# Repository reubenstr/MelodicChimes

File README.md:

# MelodicChimes

Melodic Chimes is a three string auto-tuning wall chime playing MIDI files created in MuseScore.

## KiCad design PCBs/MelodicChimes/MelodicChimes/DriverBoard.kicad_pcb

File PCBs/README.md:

# PCBs

PCBs created in the free version of DipTrace found here https://diptrace.com/

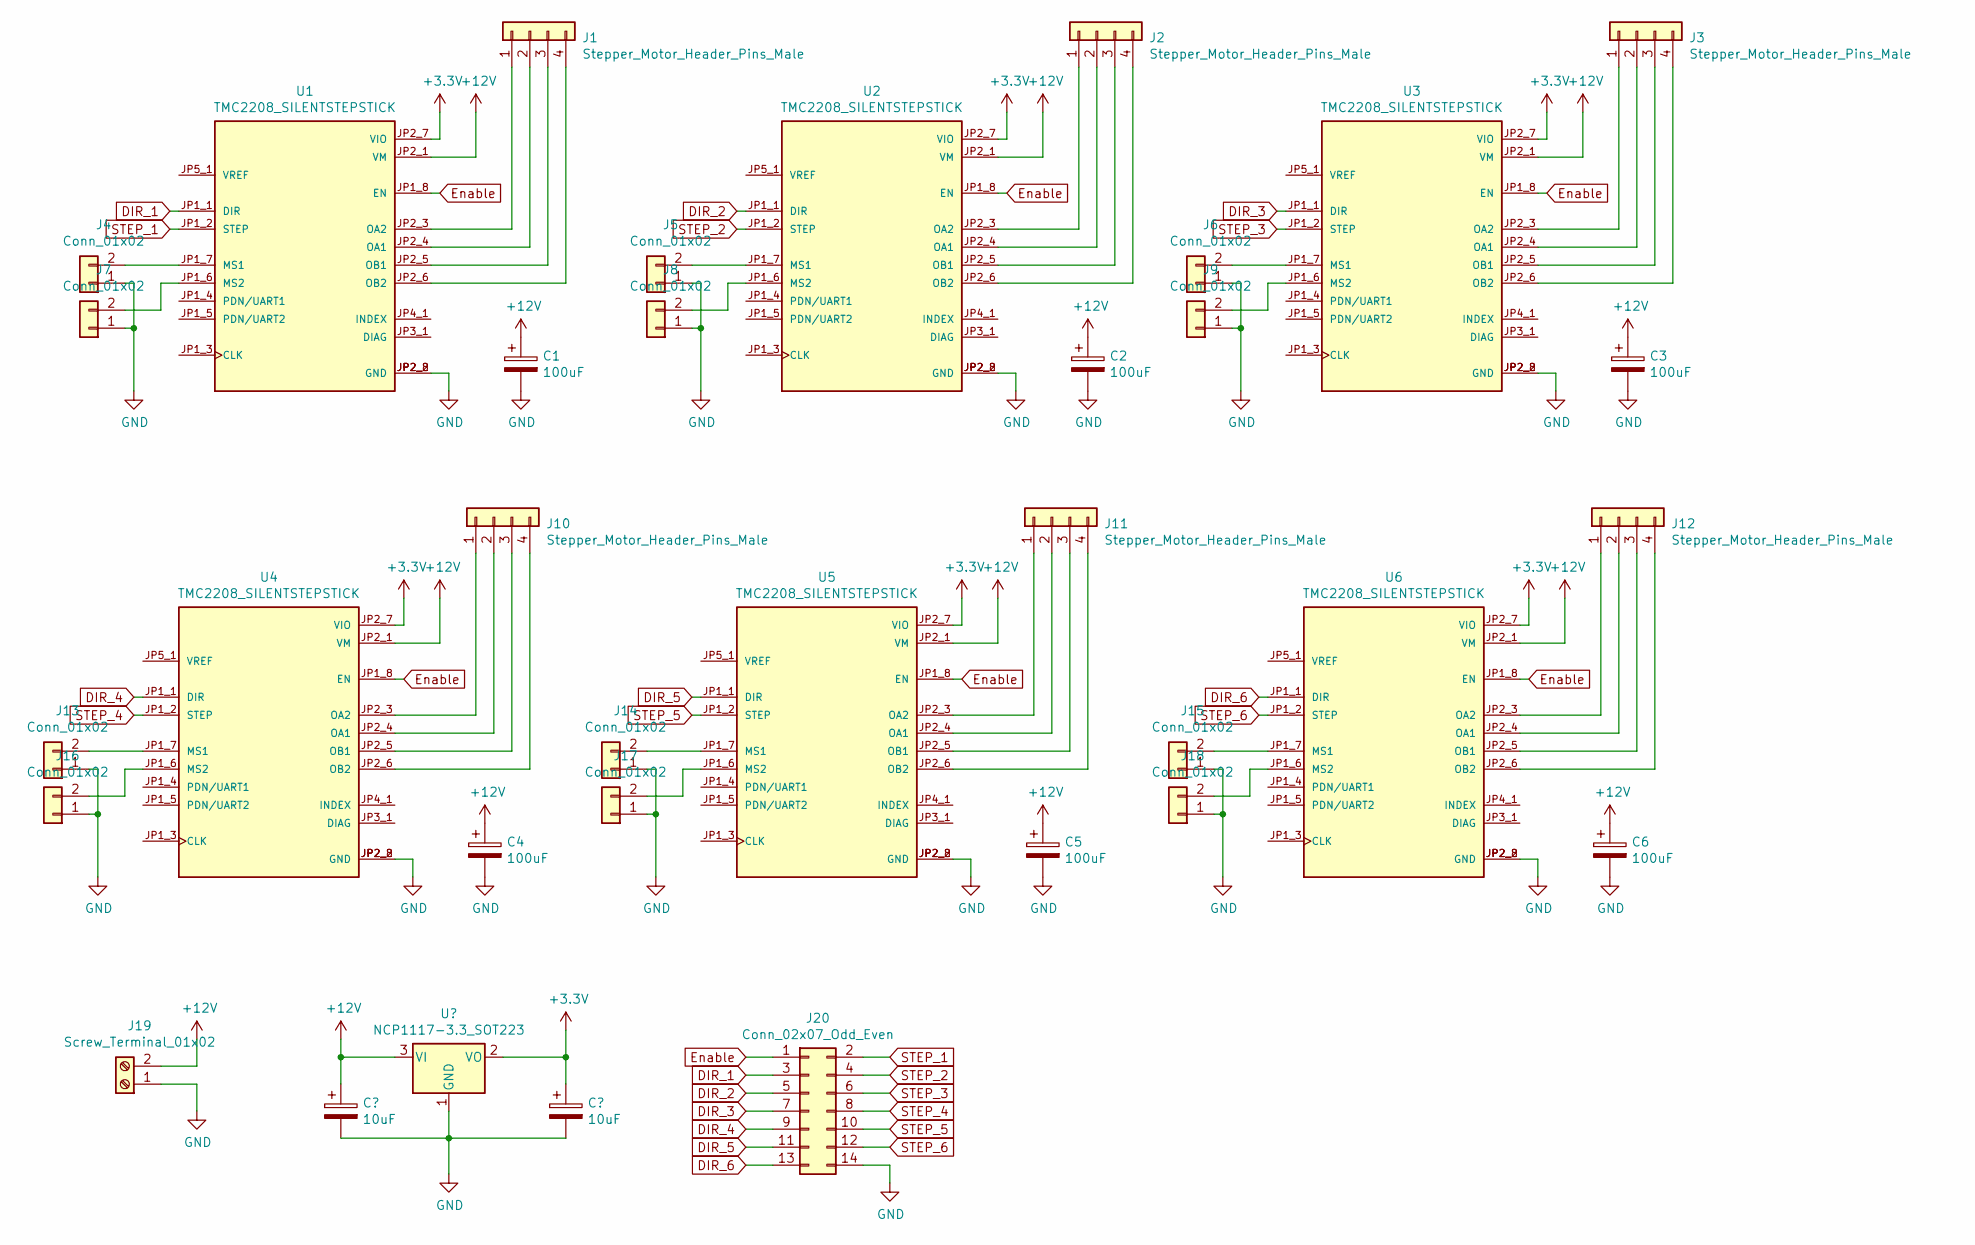
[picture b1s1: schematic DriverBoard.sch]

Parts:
C1, C2, C3, C4, C5, C6: 100uF; CP_Radial_D6.3mm_P2.50mm
J1, J2, J3, J10, J11, J12: Stepper_Motor_Header_Pins_Male; Stepper_Motor_0.100_Pins_Male
J4, J5, J6, J7, J8, J9, J13, J14, J15, J16, J17, J18: Conn_01x02; PinHeader_1x02_P2.54mm_Vertical
J19: Screw_Terminal_01x02; TerminalBlock_TE_282834-2_1x02_P2.54mm_Horizontal
J20: Conn_02x07_Odd_Even; PinHeader_2x07_P2.54mm_Vertical
U1, U2, U3, U4, U5, U6: TMC2208_SILENTSTEPSTICK; MODULE_TMC2208_SILENTSTEPSTICK; PARTREV v11

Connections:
+3V3: U1.JP2_7 (VIO), U2.JP2_7 (VIO), U3.JP2_7 (VIO), U4.JP2_7 (VIO), U5.JP2_7 (VIO), U6.JP2_7 (VIO); also elsewhere on the board
+12V: C1.1, C2.1, C3.1, C4.1, C5.1, C6.1, J19.2, U1.JP2_1 (VM), U2.JP2_1 (VM), U3.JP2_1 (VM), U4.JP2_1 (VM), U5.JP2_1 (VM), U6.JP2_1 (VM); also elsewhere on the board
DIR_1: J20.3, U1.JP1_1 (DIR)
DIR_2: J20.5, U2.JP1_1 (DIR)
DIR_3: J20.7, U3.JP1_1 (DIR)
DIR_4: J20.9, U4.JP1_1 (DIR)
DIR_5: J20.11, U5.JP1_1 (DIR)
DIR_6: J20.13, U6.JP1_1 (DIR)
Enable: J20.1, U1.JP1_8 (EN), U2.JP1_8 (EN), U3.JP1_8 (EN), U4.JP1_8 (EN), U5.JP1_8 (EN), U6.JP1_8 (EN)
GND: C1.2, C2.2, C3.2, C4.2, C5.2, C6.2, J4.1, J5.1, J6.1, J7.1, J8.1, J9.1, J13.1, J14.1, J15.1, J16.1, J17.1, J18.1, J19.1, J20.14, U1.JP2_2 (GND), U1.JP2_8 (GND), U2.JP2_2 (GND), U2.JP2_8 (GND), U3.JP2_2 (GND), U3.JP2_8 (GND), U4.JP2_2 (GND), U4.JP2_8 (GND), U5.JP2_2 (GND), U5.JP2_8 (GND), U6.JP2_2 (GND), U6.JP2_8 (GND); also elsewhere on the board
unnamed: J1.1 (1B), U1.JP2_3 (OA2)
unnamed: J1.2 (1A), U1.JP2_4 (OA1)
unnamed: J1.3 (2A), U1.JP2_5 (OB1)
unnamed: J1.4 (2B), U1.JP2_6 (OB2)
unnamed: J2.1 (1B), U2.JP2_3 (OA2)
unnamed: J2.2 (1A), U2.JP2_4 (OA1)
unnamed: J2.3 (2A), U2.JP2_5 (OB1)
unnamed: J2.4 (2B), U2.JP2_6 (OB2)
unnamed: J3.1 (1B), U3.JP2_3 (OA2)
unnamed: J3.2 (1A), U3.JP2_4 (OA1)
unnamed: J3.3 (2A), U3.JP2_5 (OB1)
unnamed: J3.4 (2B), U3.JP2_6 (OB2)
unnamed: J4.2, U1.JP1_7 (MS1)
unnamed: J5.2, U2.JP1_7 (MS1)
unnamed: J6.2, U3.JP1_7 (MS1)
unnamed: J7.2, U1.JP1_6 (MS2)
unnamed: J8.2, U2.JP1_6 (MS2)
unnamed: J9.2, U3.JP1_6 (MS2)
unnamed: J10.1 (1B), U4.JP2_3 (OA2)
unnamed: J10.2 (1A), U4.JP2_4 (OA1)
unnamed: J10.3 (2A), U4.JP2_5 (OB1)
unnamed: J10.4 (2B), U4.JP2_6 (OB2)
unnamed: J11.1 (1B), U5.JP2_3 (OA2)
unnamed: J11.2 (1A), U5.JP2_4 (OA1)
unnamed: J11.3 (2A), U5.JP2_5 (OB1)
unnamed: J11.4 (2B), U5.JP2_6 (OB2)
unnamed: J12.1 (1B), U6.JP2_3 (OA2)
unnamed: J12.2 (1A), U6.JP2_4 (OA1)
unnamed: J12.3 (2A), U6.JP2_5 (OB1)
unnamed: J12.4 (2B), U6.JP2_6 (OB2)
unnamed: J13.2, U4.JP1_7 (MS1)
unnamed: J14.2, U5.JP1_7 (MS1)
unnamed: J15.2, U6.JP1_7 (MS1)
unnamed: J16.2, U4.JP1_6 (MS2)
unnamed: J17.2, U5.JP1_6 (MS2)
unnamed: J18.2, U6.JP1_6 (MS2)
STEP_1: J20.2, U1.JP1_2 (STEP)
STEP_2: J20.4, U2.JP1_2 (STEP)
STEP_3: J20.6, U3.JP1_2 (STEP)
STEP_4: J20.8, U4.JP1_2 (STEP)
STEP_5: J20.10, U5.JP1_2 (STEP)
STEP_6: J20.12, U6.JP1_2 (STEP)

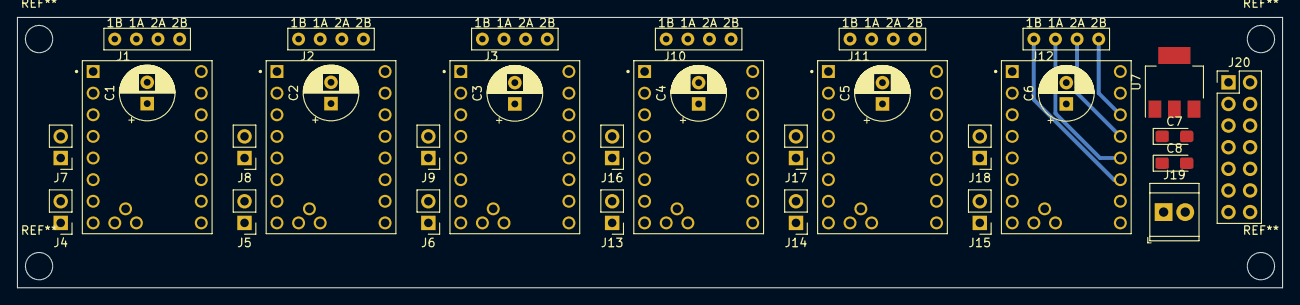
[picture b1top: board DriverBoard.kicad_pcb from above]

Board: 2 copper layers, 148.6 x 31.8 mm, 35 parts (0 on the bottom side), 52 nets.

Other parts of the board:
C7, C8: 10uF; CP_EIA-3216-12_Kemet-S_Pad1.58x1.35mm_HandSolder
U7: NCP1117-3.3_SOT223; SOT-223-3_TabPin2

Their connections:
+3V3: C8.1, U7.2; also elsewhere on the board
+12V: C7.1, U7.3; also elsewhere on the board
GND: C7.2, C8.2, U7.1; also elsewhere on the board

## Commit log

2020-01-13 First commit.
2020-01-13 Creating chime class.
2020-01-13 More chime class built.
2020-12-22 Prototyping.
2020-12-23 Continued prototyping.
2020-12-25 Prototyping. Crude melody playing.
    Need faster motors, 50RPM is way to slow. Need 200+, on the way soon. :)
2020-12-25 Prototyping. New motor control algo.
2020-12-25 Prototyping. Quicker tuning algo.
2020-12-25 Move code into classes.
2020-12-28 Prototyping. Swapping to three DC motors for control.
2020-12-28 Pick and Mute with dc motors.
2021-01-03 Change to solenoid mute.
2021-01-04 Testing n25 motor.
2021-01-05 Swap to stepper, testing.
2021-01-05 Stepper tests.
2021-01-06 State of flux between motor types.
2021-01-08 Prototyping. Working with stepper libraries.
2021-01-20 Adding pick calibration tests.
2021-01-20 Cleanup.
2021-01-21 Update.
2021-01-21 Next phase.
2021-01-22 Added note tuning by fixed steps.
2021-01-23 GLCD tests.
2021-01-23 Screen tests.
2021-01-23 GLCD Update.
2021-01-24 GLCD swap from ESP32 to TEENSY
2021-01-24 SD card, advanced labels.
2021-01-25 Label and button classes added.
2021-01-25 Class update.
2021-01-25 Change color on button presses.
2021-01-25 Label fill added.
2021-01-25 Labels and buttons working in new class format.
2021-01-25 Cleanup, class renames.
2021-01-25 Reorg.
2021-01-26 Midi parser added, working.
2021-01-26 Refactor.
2021-01-30 PCB work.
2021-01-30 PCB update.
2021-02-05 PCB dev.
2021-02-07 Backup.
2021-02-09 Adding UART.
2021-02-11 Intergrating notefreq into the chime class.
2021-02-11 Clean up.
2021-02-18 ESP32 UART test.
2021-02-19 Adding more commands to chime.
2021-02-19 Command pretune added.
2021-02-20 Commands bugfixes.
2021-02-21 Midi to chime commands ready for testing.
2021-02-21 Merged playstate and midistate into one state machine.
2021-02-21 Adding queue logic to commands being send to the chime controller.
2021-02-21 Queue updates.
2021-02-22 Queue to list for command buffer.
2021-02-26 Planetary stepper test, working very well.
2021-02-26 Testing.
2021-11-26 dev restart
    Project pickup, reconnecting hardware. Minor dev tweaks.
2021-11-29 cleanup
    removed old physical testing code
2021-11-29 cleanup
2021-12-13 mute to volume conversion
2021-12-13 clean up
2021-12-14 major cleanup
2021-12-14 add graph
2021-12-17 naming refactor
2021-12-23 cad upload, neopixel add
2021-12-26 add nameplate led control
2021-12-26 midi test files update
2021-12-27 midi update
2021-12-28 adding parameters on SD card support
2021-12-28 added wifi time fetch
2021-12-28 graphics tweak
2021-12-29 bug fix: false freq. detection due to harmonics
2022-01-08 adding communications from chimes
2022-01-08 added polynomial regression coefs to code
2022-01-08 added splash screen
2022-01-09 gfx bugged out
2022-01-09 gfx draw rework - bug fixed
2022-01-09 wifi time task added
2022-01-09 project cleanup
2022-01-09 add STLs
2022-01-27 image update
2022-02-03 image upload
2024-07-27 added image
